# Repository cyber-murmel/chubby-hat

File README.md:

# Chubby Hat
A PCB that turns the [Colorlight 5A-75B](https://www.aliexpress.com/item/32728519290.html)
into an easy to use development platform for cheap.
This project ist based on [q3k/chubby75](https://github.com/q3k/chubby75/tree/master/5a-75b).

Read more on [ hackaday.io](https://hackaday.io/project/174032-chubby-hat).

## Directory Structure
| directory  | content                                                              |
|------------|----------------------------------------------------------------------|
| source     | KiCad project directories                                            |
| production | fabrication files (Gerber, BOM, placement)                           |
| exports    | schematic and layout plots, board 3D model and renderings            |
| datasheets | component datasheets                                                 |
| assets     | board setups, component 3D models, logos                             |
| scripts    | BOM export plugins, miscellaneous helper scripts for file conversion |
| hooks      | git hooks, for example for automatic documentation export            |

### Version 0.1.0

- USB to JTAG via STM32 or FTDI
- two 3x Pmod ports

### Version 0.2.0

- USB to JTAG via extra dev board or on-board RP2040
- three 2x Pmod ports

## Automation
This repository contains a Makefile that automates PDF and Gerber export, as
well as PCB art pattern creation.

### Requirements
Apart from [KiCad 7](#kicad-version) this requires some additional software.

The Makefile calls a Python script that makes use of [sexptdata](https://pypi.org/project/sexpdata/) to parse KiCad files.
Install [Poetry](https://python-poetry.org/) and run `poetry shell` followed by `poetry install` in the root of this repositoryto set up a virtual environment with the required package(s). To re-enter this environment, simply run `poetry shell` in the root of this repository.

For PDF export you need to install [Poppler](https://poppler.freedesktop.org/).
Gerber export requires [zip](https://infozip.sourceforge.net/).
Pattern creation is implemented with [OpenSCAD](https://openscad.org/).

#### Nix(OS)
If you are using the Nix package manager, you can enter a development environment
with KiCad and all other software by running `nix-shell` in the root of this
repository.

### Export
To export all PDFs and Gerbers, simply run
```shell
make
```
PDFs and Gerbers are exported automatically when you `git commit`, if you have
[Git Hooks](#installing-git-hooks-optional) set up.

### Pattern
To recreate the pattern, first remove the pattern from the board and save it,
then run
```shell
make pattern
```
Add the new pattern graphic to the board.

### Installing Git Hooks (optional)
The [hooks](hooks) directory contains client-side [git hooks](https://git-scm.com/book/en/v2/Customizing-Git-Git-Hooks).
Currently only the pre-commit hook is used to automatically export plots.

To enable the hooks locally, run the following in the root of the repository.
```shell
git config core.hooksPath ./hooks
```

## KiCad Version
```
Version: 7.0.1, release build

Libraries:
	wxWidgets 3.2.2
	FreeType 2.12.1
	HarfBuzz 6.0.0
	FontConfig 2.14.0
	libcurl/7.87.0 OpenSSL/3.0.8 zlib/1.2.13 brotli/1.0.9 zstd/1.5.2 libidn2/2.3.2 libssh2/1.10.0 nghttp2/1.51.0

Platform: , 64 bit, Little endian, wxBase, , wayland

Build Info:
	Date: Jan  1 1980 00:00:00
	wxWidgets: 3.2.2 (wchar_t,wx containers) GTK+ 0.0
	Boost: 1.79.0
	OCC: 7.6.2
	Curl: 7.87.0
	ngspice: 37
	Compiler: GCC 12.2.0 with C++ ABI 1017

Build settings:
	KICAD_USE_EGL=ON
	KICAD_SPICE=ON
```

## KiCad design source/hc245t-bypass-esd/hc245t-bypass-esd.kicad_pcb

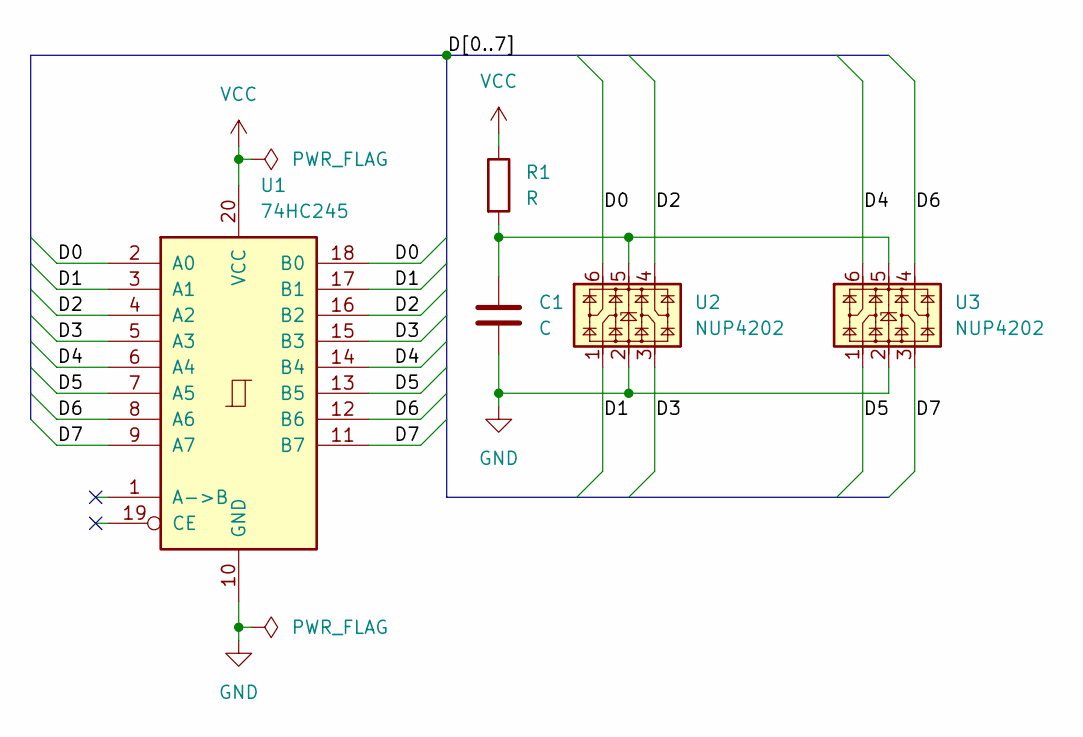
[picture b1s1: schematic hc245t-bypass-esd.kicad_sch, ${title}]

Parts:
C1: C; C_0402_1005Metric
R1: R; R_0402_1005Metric
U1: 74HC245; TSSOP-20_4.4x6.5mm_P0.65mm
U2, U3: NUP4202; SOT-363_SC-70-6

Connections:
/D0: U1.2 (A0), U1.18 (B0), U2.6
/D1: U1.3 (A1), U1.17 (B1), U2.1
/D2: U1.4 (A2), U1.16 (B2), U2.4
/D3: U1.5 (A3), U1.15 (B3), U2.3
/D4: U1.6 (A4), U1.14 (B4), U3.6
/D5: U1.7 (A5), U1.13 (B5), U3.1
/D6: U1.8 (A6), U1.12 (B6), U3.4
/D7: U1.9 (A7), U1.11 (B7), U3.3
GND: C1.2, U1.10 (GND), U2.2, U3.2
unnamed: C1.1, R1.2, U2.5, U3.5
VCC: R1.1, U1.20 (VCC)

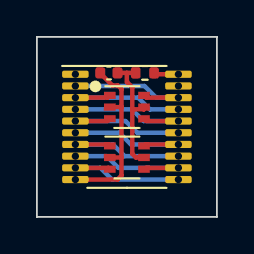
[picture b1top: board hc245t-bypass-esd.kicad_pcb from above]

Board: 2 copper layers, 10.0 x 10.0 mm, 5 parts (0 on the bottom side), 11 nets.

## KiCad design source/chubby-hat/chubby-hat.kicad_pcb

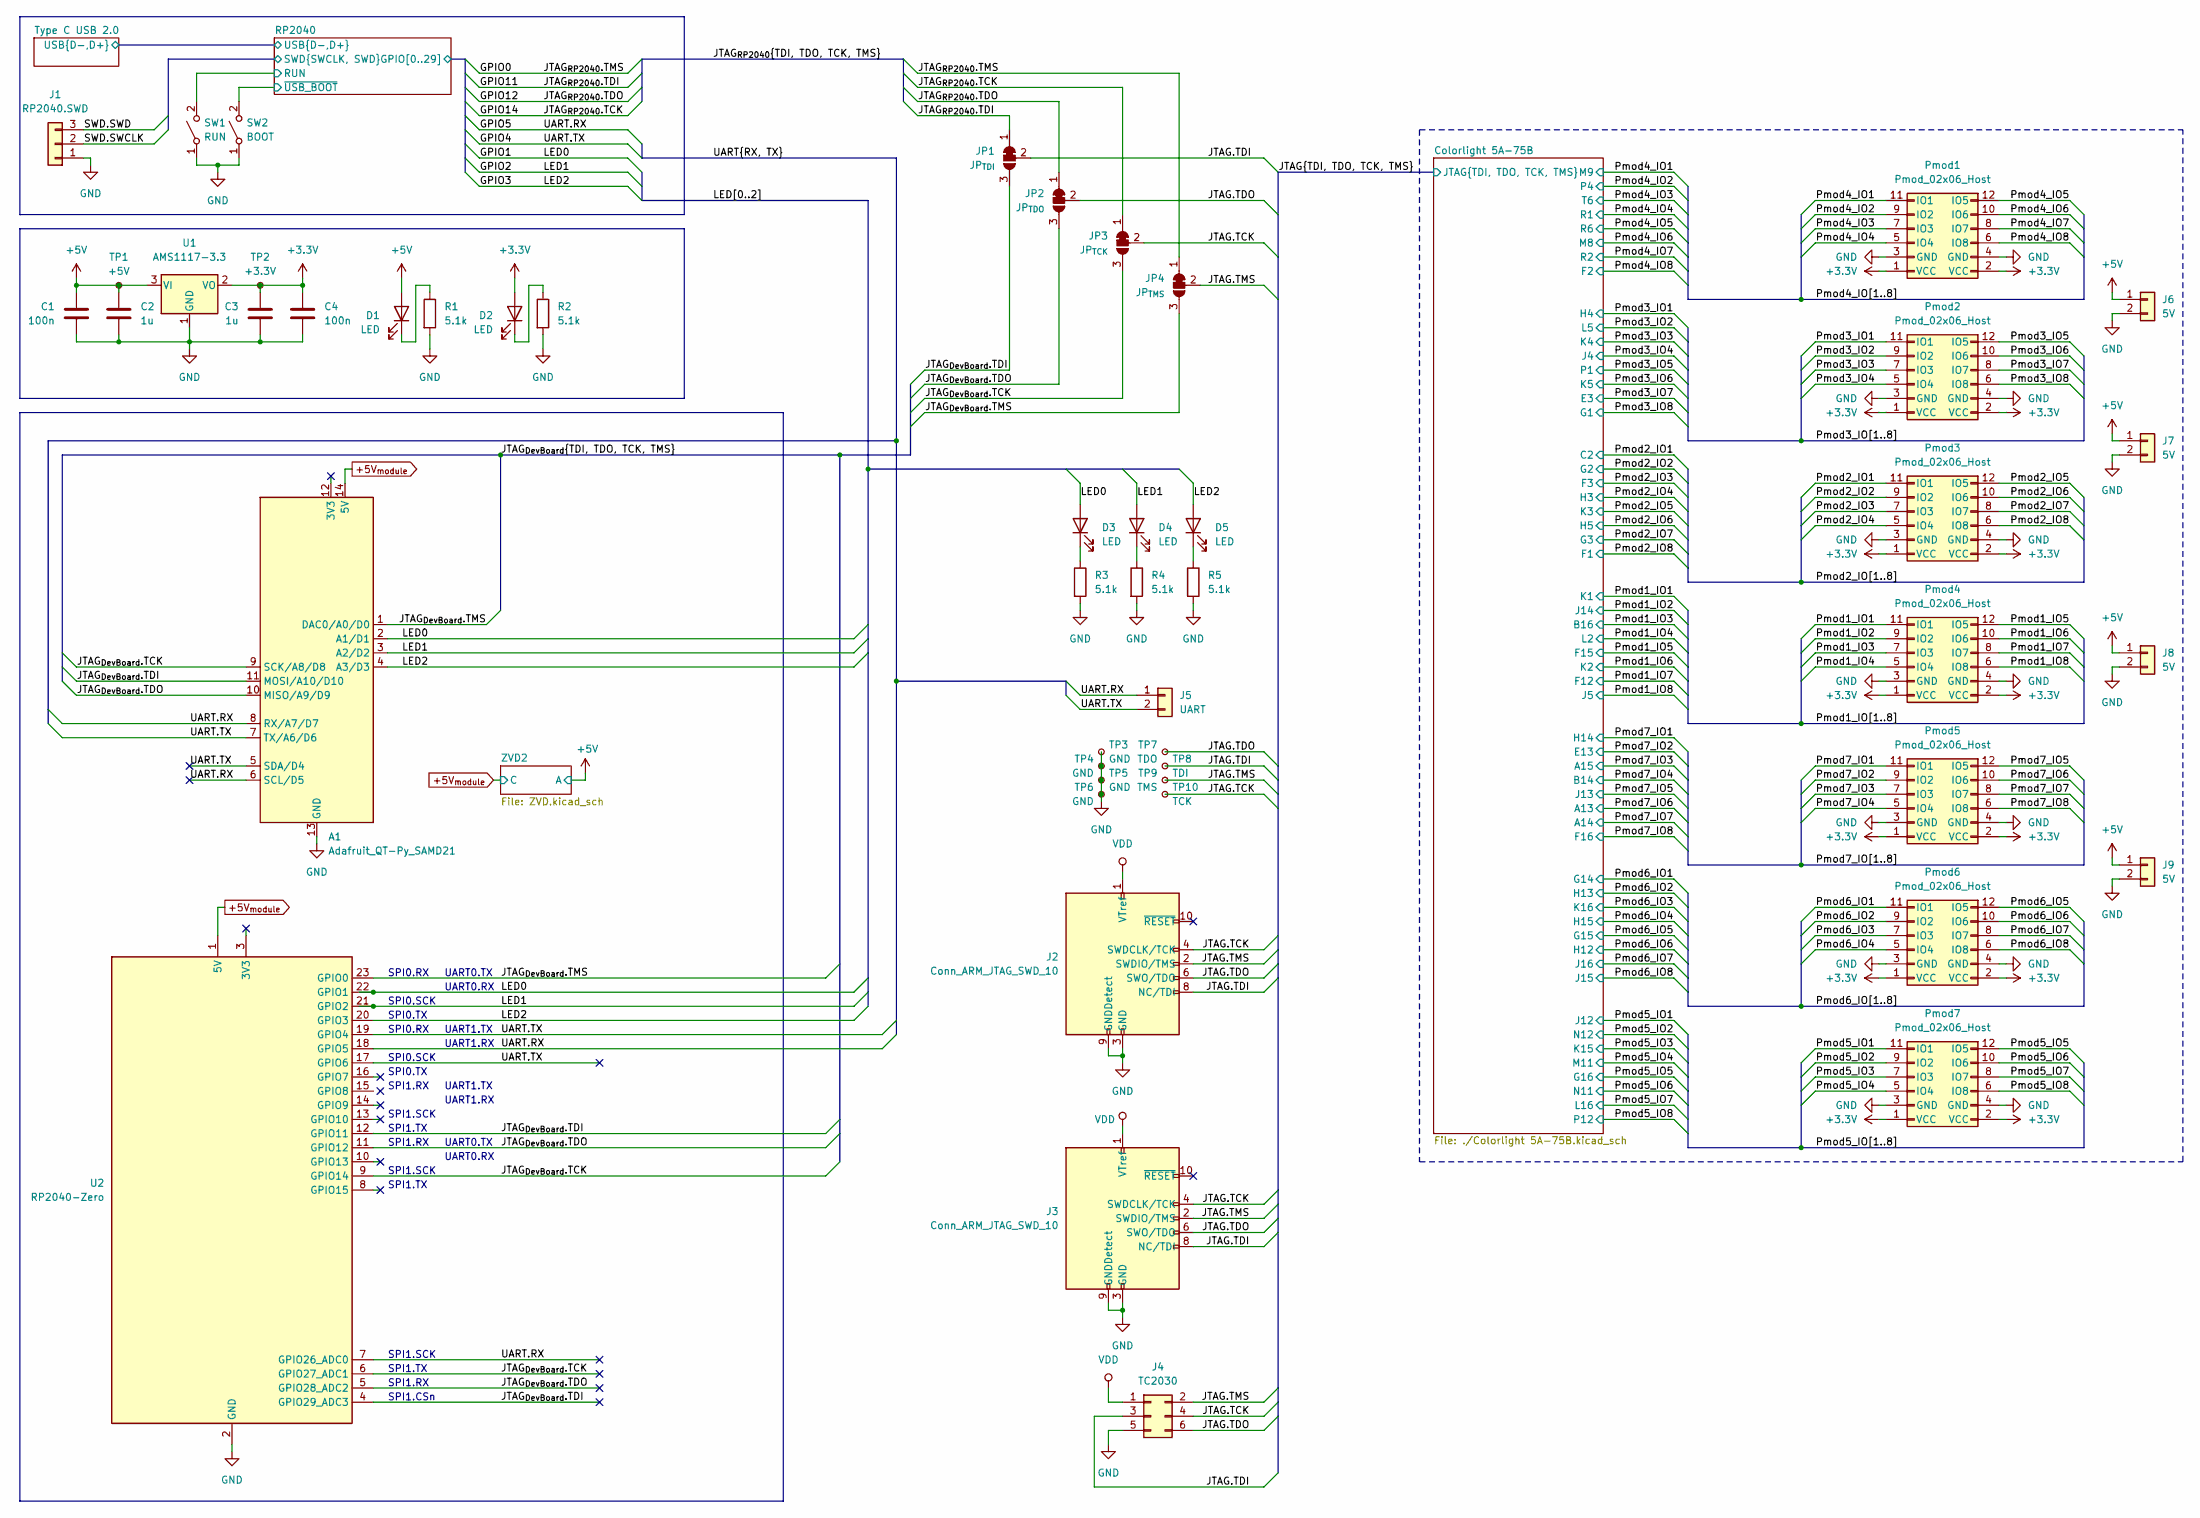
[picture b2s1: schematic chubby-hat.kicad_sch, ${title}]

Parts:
A1: Adafruit_QT-Py_SAMD21; QT-Py
C1, C4: 100n; C_0603_1608Metric
C2, C3: 1u; C_0603_1608Metric
D1, D2, D3, D4, D5: LED; LED_0603_1608Metric
J1: RP2040.SWD; PinHeader_1x03_P2.54mm_Vertical
J2: Conn_ARM_JTAG_SWD_10; IDC-Header_2x05_P2.54mm_Vertical
J3: Conn_ARM_JTAG_SWD_10; PinHeader_2x05_P1.27mm_Vertical
J4: TC2030; Tag-Connect_TC2030-IDC-FP_2x03_P1.27mm_Vertical
J5: UART; SolderWire-0.1sqmm_1x02_P3.6mm_D0.4mm_OD1mm_Relief2x
J6, J7, J8, J9: 5V; PinSocket_1x02_P2.54mm_Vertical
JP1: JP_{TDI}; SolderJumper-3_P1.3mm_Bridged12_RoundedPad1.0x1.5mm
JP2: JP_{TDO}; SolderJumper-3_P1.3mm_Bridged12_RoundedPad1.0x1.5mm
JP3: JP_{TCK}; SolderJumper-3_P1.3mm_Bridged12_RoundedPad1.0x1.5mm
JP4: JP_{TMS}; SolderJumper-3_P1.3mm_Bridged12_RoundedPad1.0x1.5mm
Pmod1, Pmod2, Pmod3, Pmod4, Pmod5, Pmod6, Pmod7: Pmod_02x06_Host; PinSocket_2x06_P2.54mm_Horizontal
R1, R2, R3, R4, R5: 5.1k; R_0603_1608Metric
SW1: RUN; SW_Push_1P1T_NO_6x6mm_H9.5mm
SW2: BOOT; SW_Push_1P1T_NO_6x6mm_H9.5mm
TP1: +5V; TestPoint_Pad_D1.0mm
TP2: +3.3V; TestPoint_Pad_D1.0mm
TP3, TP4, TP5, TP6: GND; TestPoint_Pad_D1.0mm
TP7: TDO; TestPoint_Pad_D1.0mm
TP8: TDI; TestPoint_Pad_D1.0mm
TP9: TMS; TestPoint_Pad_D1.0mm
TP10: TCK; TestPoint_Pad_D1.0mm
U1: AMS1117-3.3; SOT-223-3_TabPin2
U2: RP2040-Zero

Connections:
+5V: C1.2, C2.2, D1.2 (A), J6.1, J7.1, J8.1, J9.1, TP1.1, U1.3 (VI); also elsewhere on the board
+5V_{module}: A1.14 (5V), U2.1 (5V); also elsewhere on the board
/JTAG.TCK: J2.4 (SWDCLK/TCK), J3.4 (SWDCLK/TCK), J4.4, JP3.2 (C), TP10.1; also elsewhere on the board
/JTAG.TDI: J2.8 (NC/TDI), J3.8 (NC/TDI), J4.3, JP1.2 (C), TP8.1; also elsewhere on the board
/JTAG.TDO: J2.6 (SWO/TDO), J3.6 (SWO/TDO), J4.6, JP2.2 (C), TP7.1; also elsewhere on the board
/JTAG.TMS: J2.2 (SWDIO/TMS), J3.2 (SWDIO/TMS), J4.2, JP4.2 (C), TP9.1; also elsewhere on the board
/JTAG_{DevBoard}.TCK: A1.9 (SCK/A8/D8), JP3.3 (B), U2.6 (GPIO27_ADC1), U2.9 (GPIO14); also elsewhere on the board
/JTAG_{DevBoard}.TDI: A1.11 (MOSI/A10/D10), JP1.3 (B), U2.4 (GPIO29_ADC3), U2.12 (GPIO11); also elsewhere on the board
/JTAG_{DevBoard}.TDO: A1.10 (MISO/A9/D9), JP2.3 (B), U2.5 (GPIO28_ADC2), U2.11 (GPIO12); also elsewhere on the board
/JTAG_{DevBoard}.TMS: A1.1 (DAC0/A0/D0), JP4.3 (B), U2.23 (GPIO0); also elsewhere on the board
/Pmod1_IO1: Pmod4.11 (IO1); also elsewhere on the board
/Pmod1_IO2: Pmod4.9 (IO2); also elsewhere on the board
/Pmod1_IO3: Pmod4.7 (IO3); also elsewhere on the board
/Pmod1_IO4: Pmod4.5 (IO4); also elsewhere on the board
/Pmod1_IO5: Pmod4.12 (IO5); also elsewhere on the board
/Pmod1_IO6: Pmod4.10 (IO6); also elsewhere on the board
/Pmod1_IO7: Pmod4.8 (IO7); also elsewhere on the board
/Pmod1_IO8: Pmod4.6 (IO8); also elsewhere on the board
/Pmod2_IO1: Pmod3.11 (IO1); also elsewhere on the board
/Pmod2_IO2: Pmod3.9 (IO2); also elsewhere on the board
/Pmod2_IO3: Pmod3.7 (IO3); also elsewhere on the board
/Pmod2_IO4: Pmod3.5 (IO4); also elsewhere on the board
/Pmod2_IO5: Pmod3.12 (IO5); also elsewhere on the board
/Pmod2_IO6: Pmod3.10 (IO6); also elsewhere on the board
/Pmod2_IO7: Pmod3.8 (IO7); also elsewhere on the board
/Pmod2_IO8: Pmod3.6 (IO8); also elsewhere on the board
/Pmod3_IO1: Pmod2.11 (IO1); also elsewhere on the board
/Pmod3_IO2: Pmod2.9 (IO2); also elsewhere on the board
/Pmod3_IO3: Pmod2.7 (IO3); also elsewhere on the board
/Pmod3_IO4: Pmod2.5 (IO4); also elsewhere on the board
/Pmod3_IO5: Pmod2.12 (IO5); also elsewhere on the board
/Pmod3_IO6: Pmod2.10 (IO6); also elsewhere on the board
/Pmod3_IO7: Pmod2.8 (IO7); also elsewhere on the board
/Pmod3_IO8: Pmod2.6 (IO8); also elsewhere on the board
/Pmod4_IO1: Pmod1.11 (IO1); also elsewhere on the board
/Pmod4_IO2: Pmod1.9 (IO2); also elsewhere on the board
/Pmod4_IO3: Pmod1.7 (IO3); also elsewhere on the board
/Pmod4_IO4: Pmod1.5 (IO4); also elsewhere on the board
/Pmod4_IO5: Pmod1.12 (IO5); also elsewhere on the board
/Pmod4_IO6: Pmod1.10 (IO6); also elsewhere on the board
/Pmod4_IO7: Pmod1.8 (IO7); also elsewhere on the board
/Pmod4_IO8: Pmod1.6 (IO8); also elsewhere on the board
/Pmod5_IO1: Pmod7.11 (IO1); also elsewhere on the board
/Pmod5_IO2: Pmod7.9 (IO2); also elsewhere on the board
/Pmod5_IO3: Pmod7.7 (IO3); also elsewhere on the board
/Pmod5_IO4: Pmod7.5 (IO4); also elsewhere on the board
/Pmod5_IO5: Pmod7.12 (IO5); also elsewhere on the board
/Pmod5_IO6: Pmod7.10 (IO6); also elsewhere on the board
/Pmod5_IO7: Pmod7.8 (IO7); also elsewhere on the board
/Pmod5_IO8: Pmod7.6 (IO8); also elsewhere on the board
/Pmod6_IO1: Pmod6.11 (IO1); also elsewhere on the board
/Pmod6_IO2: Pmod6.9 (IO2); also elsewhere on the board
/Pmod6_IO3: Pmod6.7 (IO3); also elsewhere on the board
/Pmod6_IO4: Pmod6.5 (IO4); also elsewhere on the board
/Pmod6_IO5: Pmod6.12 (IO5); also elsewhere on the board
/Pmod6_IO6: Pmod6.10 (IO6); also elsewhere on the board
/Pmod6_IO7: Pmod6.8 (IO7); also elsewhere on the board
/Pmod6_IO8: Pmod6.6 (IO8); also elsewhere on the board
/Pmod7_IO1: Pmod5.11 (IO1); also elsewhere on the board
/Pmod7_IO2: Pmod5.9 (IO2); also elsewhere on the board
/Pmod7_IO3: Pmod5.7 (IO3); also elsewhere on the board
/Pmod7_IO4: Pmod5.5 (IO4); also elsewhere on the board
/Pmod7_IO5: Pmod5.12 (IO5); also elsewhere on the board
/Pmod7_IO6: Pmod5.10 (IO6); also elsewhere on the board
/Pmod7_IO7: Pmod5.8 (IO7); also elsewhere on the board
/Pmod7_IO8: Pmod5.6 (IO8); also elsewhere on the board
/RP2040/GPIO1: A1.2 (A1/D1), D3.2 (A), U2.22 (GPIO1); also elsewhere on the board
/RP2040/GPIO2: A1.3 (A2/D2), D4.2 (A), U2.21 (GPIO2); also elsewhere on the board
/RP2040/GPIO3: A1.4 (A3/D3), D5.2 (A), U2.20 (GPIO3); also elsewhere on the board
/RP2040/GPIO4: A1.5 (SDA/D4), A1.7 (TX/A6/D6), J5.2, U2.17 (GPIO6), U2.19 (GPIO4); also elsewhere on the board
/RP2040/GPIO5: A1.6 (SCL/D5), A1.8 (RX/A7/D7), J5.1, U2.7 (GPIO26_ADC0), U2.18 (GPIO5); also elsewhere on the board
/RP2040/RUN: SW1.2 (B); also elsewhere on the board
/RP2040/SWD.SWCLK: J1.2; also elsewhere on the board
/RP2040/SWD.SWD: J1.3; also elsewhere on the board
/RP2040/~USB_BOOT: SW2.2 (B); also elsewhere on the board
GND: A1.13 (GND), C1.1, C2.1, C3.1, C4.1, J1.1, J2.3 (GND), J2.5 (GND), J2.9 (GNDDetect), J3.3 (GND), J3.5 (GND), J3.9 (GNDDetect), J4.5, J6.2, J7.2, J8.2, J9.2, Pmod1.3 (GND), Pmod1.4 (GND), Pmod2.3 (GND), Pmod2.4 (GND), Pmod3.3 (GND), Pmod3.4 (GND), Pmod4.3 (GND), Pmod4.4 (GND), Pmod5.3 (GND), Pmod5.4 (GND), Pmod6.3 (GND), Pmod6.4 (GND), Pmod7.3 (GND), Pmod7.4 (GND), R1.2, R2.2, R3.2, R4.2, R5.2, SW1.1 (A), SW2.1 (A), TP3.1, TP4.1, TP5.1, TP6.1, U1.1 (GND), U2.2 (GND); also elsewhere on the board
unnamed: D1.1 (K), R1.1
unnamed: D2.1 (K), R2.1
unnamed: D3.1 (K), R3.1
unnamed: D4.1 (K), R4.1
unnamed: D5.1 (K), R5.1
VDD: J2.1 (VTref), J3.1 (VTref), J4.1; also elsewhere on the board

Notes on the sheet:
SPI1.TX
SPI0.SCK
UART0.TX
UART1.RX
UART1.TX
SPI1.CSn
UART0.RX
SPI1.RX
SPI0.RX
SPI1.SCK
SPI0.TX

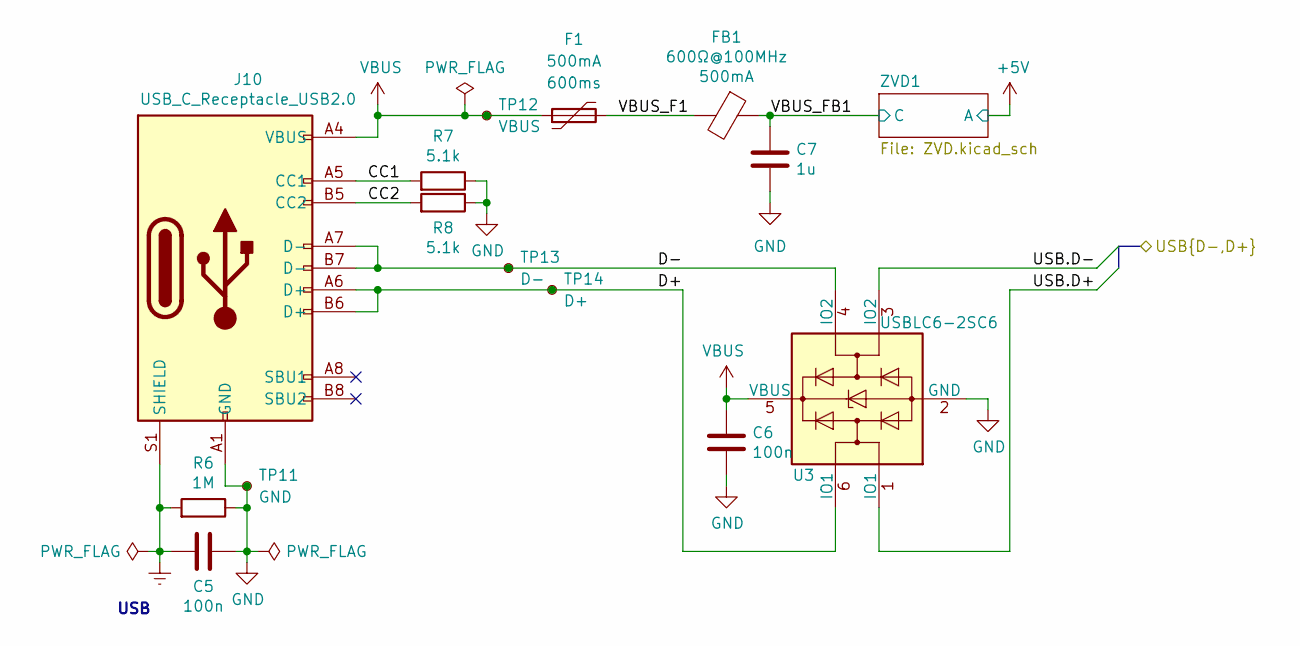
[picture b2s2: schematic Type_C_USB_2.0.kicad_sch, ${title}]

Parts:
C5, C6: 100n; C_0603_1608Metric
C7: 1u; C_0603_1608Metric
F1: 500mA; R_0603_1608Metric; MPN TLC-FSMD020; LCSC C261935
FB1: 600Ω@100MHz; L_0603_1608Metric; MPN FCM1608KF-601T05
J10: USB_C_Receptacle_USB2.0; USB_C_Receptacle_HRO_TYPE-C-31-D-09
R6: 1M; R_0603_1608Metric
R7, R8: 5.1k; R_0603_1608Metric
TP11: GND; TestPoint_Pad_D1.0mm
TP12: VBUS; TestPoint_Pad_D1.0mm
TP13: D-; TestPoint_Pad_D1.0mm
TP14: D+; TestPoint_Pad_D1.0mm
U3: USBLC6-2SC6; SOT-23-6

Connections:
/RP2040/USB.D+: U3.1 (IO1); also elsewhere on the board
/RP2040/USB.D-: U3.3 (IO2); also elsewhere on the board
/Type C USB 2.0/CC1: J10.A5 (CC1), R7.2
/Type C USB 2.0/CC2: J10.B5 (CC2), R8.2
/Type C USB 2.0/D+: J10.A6 (D+), J10.B6 (D+), TP14.1, U3.6 (IO1)
/Type C USB 2.0/D-: J10.A7 (D-), J10.B7 (D-), TP13.1, U3.4 (IO2)
/Type C USB 2.0/VBUS_F1: F1.2, FB1.2
/Type C USB 2.0/VBUS_FB1: C7.2, FB1.1; also elsewhere on the board
Earth: C5.1, J10.S1 (SHIELD), R6.2
GND: C5.2, C6.1, C7.1, J10.A1 (GND), J10.A12 (GND), J10.B1 (GND), J10.B12 (GND), R6.1, R7.1, R8.1, TP11.1, U3.2 (GND); also elsewhere on the board
VBUS: C6.2, F1.1, J10.A4 (VBUS), J10.A9 (VBUS), J10.B4 (VBUS), J10.B9 (VBUS), TP12.1, U3.5 (VBUS)

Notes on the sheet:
USB

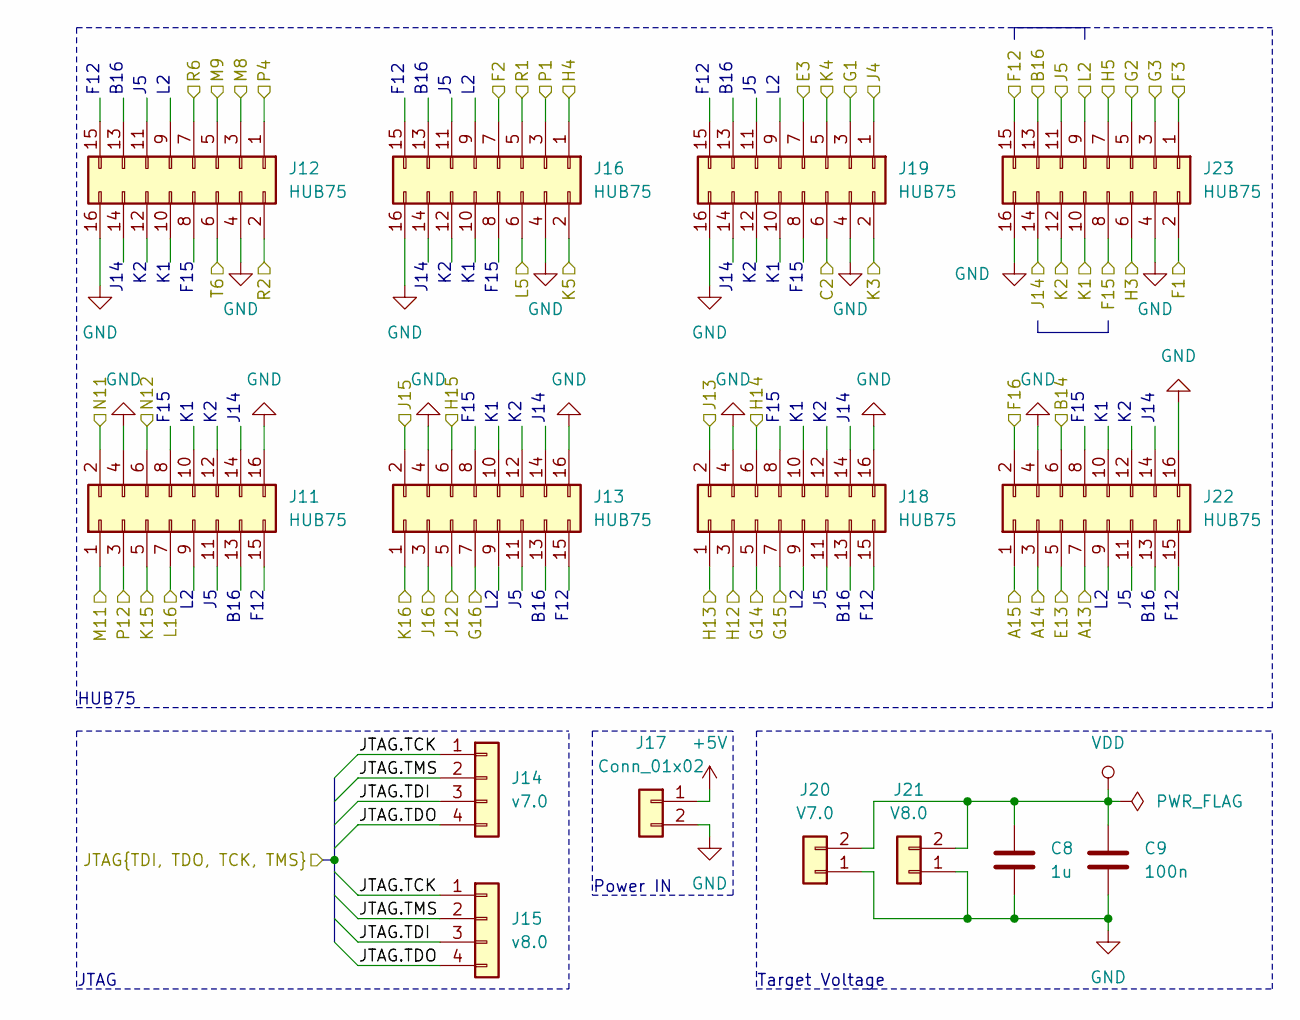
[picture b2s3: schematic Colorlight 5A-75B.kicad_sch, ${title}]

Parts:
C8: 1u; C_0603_1608Metric
C9: 100n; C_0603_1608Metric
J11, J12, J13, J16, J18, J19, J22, J23: HUB75; PinSocket_2x08_P2.54mm_Vertical
J14: v7.0; PinHeader_1x04_P2.54mm_Vertical
J15: v8.0; PinHeader_1x04_P2.54mm_Vertical
J17: Conn_01x02; SolderWire-0.5sqmm_1x02_P4.6mm_D0.9mm_OD2.1mm_Relief
J20: V7.0; PinHeader_1x02_P2.54mm_Vertical
J21: V8.0; PinHeader_1x02_P2.54mm_Vertical

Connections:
+5V: J17.1; also elsewhere on the board
/JTAG.TCK: J14.1, J15.1; also elsewhere on the board
/JTAG.TDI: J14.3, J15.3; also elsewhere on the board
/JTAG.TDO: J14.4, J15.4; also elsewhere on the board
/JTAG.TMS: J14.2, J15.2; also elsewhere on the board
/Pmod1_IO1: J23.10; also elsewhere on the board
/Pmod1_IO2: J23.14; also elsewhere on the board
/Pmod1_IO3: J23.13; also elsewhere on the board
/Pmod1_IO4: J23.9; also elsewhere on the board
/Pmod1_IO5: J23.8; also elsewhere on the board
/Pmod1_IO6: J23.12; also elsewhere on the board
/Pmod1_IO7: J23.15; also elsewhere on the board
/Pmod1_IO8: J23.11; also elsewhere on the board
/Pmod2_IO1: J19.6; also elsewhere on the board
/Pmod2_IO2: J23.5; also elsewhere on the board
/Pmod2_IO3: J23.1; also elsewhere on the board
/Pmod2_IO4: J23.6; also elsewhere on the board
/Pmod2_IO5: J19.2; also elsewhere on the board
/Pmod2_IO6: J23.7; also elsewhere on the board
/Pmod2_IO7: J23.3; also elsewhere on the board
/Pmod2_IO8: J23.2; also elsewhere on the board
/Pmod3_IO1: J16.1; also elsewhere on the board
/Pmod3_IO2: J16.6; also elsewhere on the board
/Pmod3_IO3: J19.5; also elsewhere on the board
/Pmod3_IO4: J19.1; also elsewhere on the board
/Pmod3_IO5: J16.3; also elsewhere on the board
/Pmod3_IO6: J16.2; also elsewhere on the board
/Pmod3_IO7: J19.7; also elsewhere on the board
/Pmod3_IO8: J19.3; also elsewhere on the board
/Pmod4_IO1: J12.5; also elsewhere on the board
/Pmod4_IO2: J12.1; also elsewhere on the board
/Pmod4_IO3: J12.6; also elsewhere on the board
/Pmod4_IO4: J16.5; also elsewhere on the board
/Pmod4_IO5: J12.7; also elsewhere on the board
/Pmod4_IO6: J12.3; also elsewhere on the board
/Pmod4_IO7: J12.2; also elsewhere on the board
/Pmod4_IO8: J16.7; also elsewhere on the board
/Pmod5_IO1: J13.5; also elsewhere on the board
/Pmod5_IO2: J11.6; also elsewhere on the board
/Pmod5_IO3: J11.5; also elsewhere on the board
/Pmod5_IO4: J11.1; also elsewhere on the board
/Pmod5_IO5: J13.7; also elsewhere on the board
/Pmod5_IO6: J11.2; also elsewhere on the board
/Pmod5_IO7: J11.7; also elsewhere on the board
/Pmod5_IO8: J11.3; also elsewhere on the board
/Pmod6_IO1: J18.5; also elsewhere on the board
/Pmod6_IO2: J18.1; also elsewhere on the board
/Pmod6_IO3: J13.1; also elsewhere on the board
/Pmod6_IO4: J13.6; also elsewhere on the board
/Pmod6_IO5: J18.7; also elsewhere on the board
/Pmod6_IO6: J18.3; also elsewhere on the board
/Pmod6_IO7: J13.3; also elsewhere on the board
/Pmod6_IO8: J13.2; also elsewhere on the board
/Pmod7_IO1: J18.6; also elsewhere on the board
/Pmod7_IO2: J22.5; also elsewhere on the board
/Pmod7_IO3: J22.1; also elsewhere on the board
/Pmod7_IO4: J22.6; also elsewhere on the board
/Pmod7_IO5: J18.2; also elsewhere on the board
/Pmod7_IO6: J22.7; also elsewhere on the board
/Pmod7_IO7: J22.3; also elsewhere on the board
/Pmod7_IO8: J22.2; also elsewhere on the board
GND: C8.1, C9.1, J11.4, J11.16, J12.4, J12.16, J13.4, J13.16, J16.4, J16.16, J17.2, J18.4, J18.16, J19.4, J19.16, J20.1, J21.1, J22.4, J22.16, J23.4, J23.16; also elsewhere on the board
VDD: C8.2, C9.2, J20.2, J21.2; also elsewhere on the board

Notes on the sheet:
J14
Target Voltage
F12
B16
HUB75
F15
Power IN
JTAG

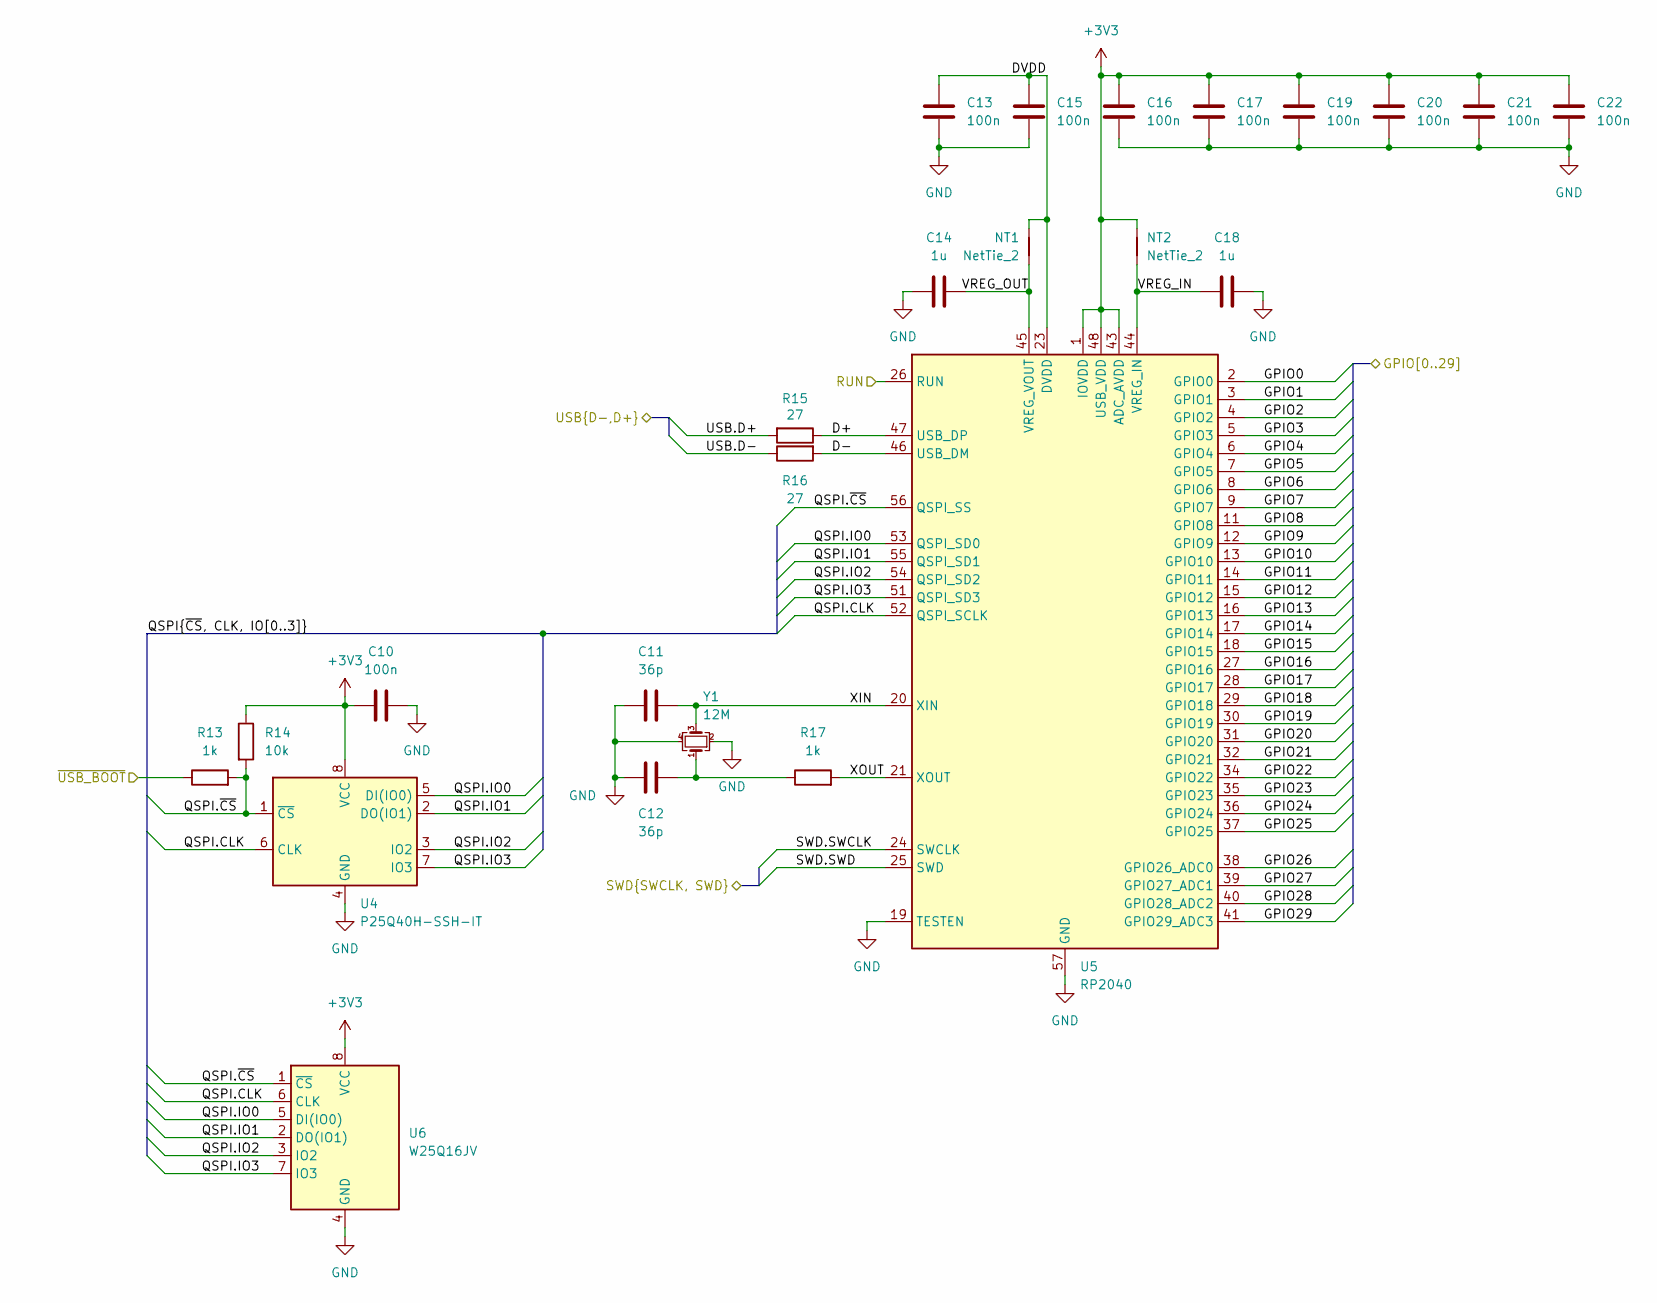
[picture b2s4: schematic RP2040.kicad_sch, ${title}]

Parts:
C10, C13, C15, C16, C17, C19, C20, C21, C22: 100n; C_0603_1608Metric
C11, C12: 36p; C_0603_1608Metric
C14, C18: 1u; C_0603_1608Metric
NT1, NT2: NetTie_2; NetTie-2_SMD_Pad0.5mm
R13, R17: 1k; R_0603_1608Metric
R14: 10k; R_0603_1608Metric
R15, R16: 27; R_0603_1608Metric
U4: P25Q40H-SSH-IT; SOIC-8_5.23x5.23mm_P1.27mm
U5: RP2040; QFN-56-1EP_7x7mm_P0.4mm_EP3.2x3.2mm
U6: W25Q16JV; VSSOP-8_2.3x2mm_P0.5mm
Y1: 12M; Crystal_SMD_3225-4Pin_3.2x2.5mm; MPN X322512MSB4SI

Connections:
/RP2040/D+: R15.1, U5.47 (USB_DP)
/RP2040/D-: R16.2, U5.46 (USB_DM)
/RP2040/DVDD: C13.1, C15.1, NT1.2, U5.23 (DVDD), U5.50 (DVDD)
/RP2040/GPIO0: U5.2 (GPIO0); also elsewhere on the board
/RP2040/GPIO1: U5.3 (GPIO1); also elsewhere on the board
/RP2040/GPIO2: U5.4 (GPIO2); also elsewhere on the board
/RP2040/GPIO3: U5.5 (GPIO3); also elsewhere on the board
/RP2040/GPIO4: U5.6 (GPIO4); also elsewhere on the board
/RP2040/GPIO5: U5.7 (GPIO5); also elsewhere on the board
/RP2040/GPIO6: U5.8 (GPIO6)
/RP2040/GPIO7: U5.9 (GPIO7)
/RP2040/GPIO8: U5.11 (GPIO8)
/RP2040/GPIO9: U5.12 (GPIO9)
/RP2040/GPIO10: U5.13 (GPIO10)
/RP2040/GPIO11: U5.14 (GPIO11); also elsewhere on the board
/RP2040/GPIO12: U5.15 (GPIO12); also elsewhere on the board
/RP2040/GPIO13: U5.16 (GPIO13)
/RP2040/GPIO14: U5.17 (GPIO14); also elsewhere on the board
/RP2040/GPIO15: U5.18 (GPIO15)
/RP2040/GPIO16: U5.27 (GPIO16)
/RP2040/GPIO17: U5.28 (GPIO17)
/RP2040/GPIO18: U5.29 (GPIO18)
/RP2040/GPIO19: U5.30 (GPIO19)
/RP2040/GPIO20: U5.31 (GPIO20)
/RP2040/GPIO21: U5.32 (GPIO21)
/RP2040/GPIO22: U5.34 (GPIO22)
/RP2040/GPIO23: U5.35 (GPIO23)
/RP2040/GPIO24: U5.36 (GPIO24)
/RP2040/GPIO25: U5.37 (GPIO25)
/RP2040/GPIO26: U5.38 (GPIO26_ADC0)
/RP2040/GPIO27: U5.39 (GPIO27_ADC1)
/RP2040/GPIO28: U5.40 (GPIO28_ADC2)
/RP2040/GPIO29: U5.41 (GPIO29_ADC3)
/RP2040/QSPI.CLK: U4.6 (CLK), U5.52 (QSPI_SCLK), U6.6 (CLK)
/RP2040/QSPI.IO0: U4.5 (DI(IO0)), U5.53 (QSPI_SD0), U6.5 (DI(IO0))
/RP2040/QSPI.IO1: U4.2 (DO(IO1)), U5.55 (QSPI_SD1), U6.2 (DO(IO1))
/RP2040/QSPI.IO2: U4.3 (IO2), U5.54 (QSPI_SD2), U6.3 (IO2)
/RP2040/QSPI.IO3: U4.7 (IO3), U5.51 (QSPI_SD3), U6.7 (IO3)
/RP2040/QSPI.~CS: R13.2, R14.2, U4.1 (~CS), U5.56 (QSPI_SS), U6.1 (~CS)
/RP2040/RUN: U5.26 (RUN); also elsewhere on the board
/RP2040/SWD.SWCLK: U5.24 (SWCLK); also elsewhere on the board
/RP2040/SWD.SWD: U5.25 (SWD); also elsewhere on the board
/RP2040/USB.D+: R15.2; also elsewhere on the board
/RP2040/USB.D-: R16.1; also elsewhere on the board
/RP2040/VREG_IN: C18.1, NT2.2, U5.44 (VREG_IN)
/RP2040/VREG_OUT: C14.1, NT1.1, U5.45 (VREG_VOUT)
/RP2040/XIN: C11.1, U5.20 (XIN), Y1.3
/RP2040/XOUT: R17.2, U5.21 (XOUT)
/RP2040/~USB_BOOT: R13.1; also elsewhere on the board
GND: C10.2, C11.2, C12.2, C13.2, C14.2, C15.2, C16.2, C17.2, C18.2, C19.2, C20.2, C21.2, C22.2, U4.4 (GND), U5.19 (TESTEN), U5.57 (GND), U6.4 (GND), Y1.2, Y1.4; also elsewhere on the board
unnamed: C12.1, R17.1, Y1.1

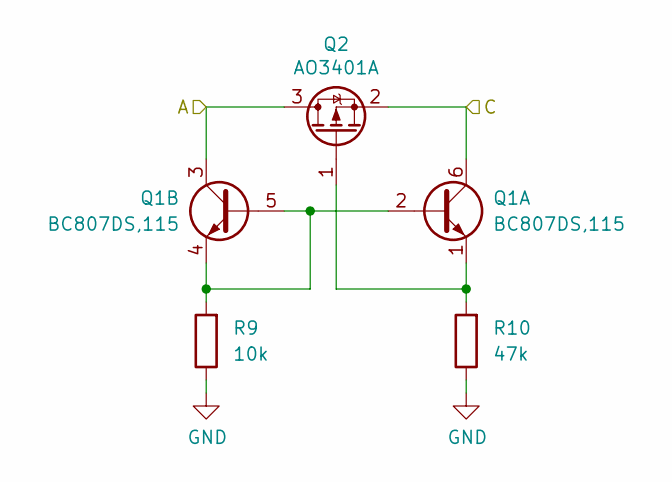
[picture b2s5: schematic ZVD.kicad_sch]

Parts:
Q1: BC807DS,115; SC-74-6_1.5x2.9mm_P0.95mm
Q2: AO3401A; SOT-23
R9: 10k; R_0603_1608Metric
R10: 47k; R_0603_1608Metric

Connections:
+5V: Q1.3 (C2), Q2.3 (D); also elsewhere on the board
/Type C USB 2.0/VBUS_FB1: Q1.6 (C1), Q2.2 (S); also elsewhere on the board
GND: R9.1, R10.1; also elsewhere on the board
unnamed: Q1.2 (B1), Q1.4 (E2), Q1.5 (B2), R9.2
unnamed: Q1.1 (E1), Q2.1 (G), R10.2

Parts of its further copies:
Q3: BC807DS,115; SC-74-6_1.5x2.9mm_P0.95mm
Q4: AO3401A; SOT-23
R11: 10k; R_0603_1608Metric
R12: 47k; R_0603_1608Metric

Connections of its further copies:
+5V: Q3.3 (C2), Q4.3 (D); also elsewhere on the board
+5V_{module}: Q3.6 (C1), Q4.2 (S); also elsewhere on the board
GND: R11.1, R12.1; also elsewhere on the board
unnamed: Q3.2 (B1), Q3.4 (E2), Q3.5 (B2), R11.2
unnamed: Q3.1 (E1), Q4.1 (G), R12.2

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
